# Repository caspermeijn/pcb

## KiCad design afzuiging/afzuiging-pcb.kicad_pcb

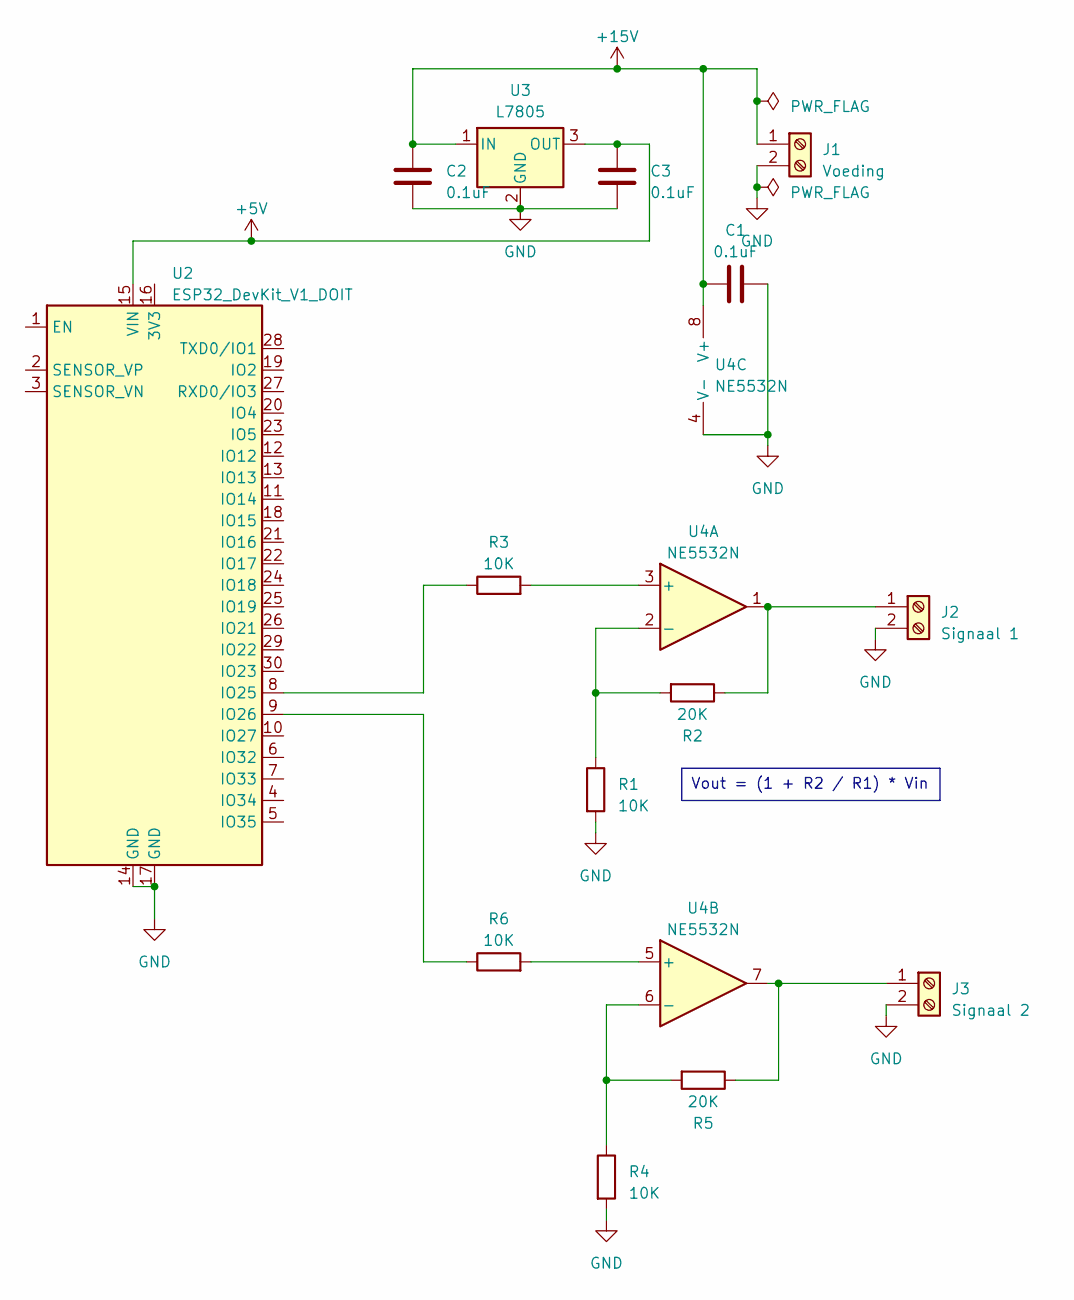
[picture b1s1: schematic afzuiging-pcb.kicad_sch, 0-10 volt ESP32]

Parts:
C1, C2, C3: 0.1uF; C_Disc_D4.7mm_W2.5mm_P5.00mm
J1: Voeding; TerminalBlock_RND_205-00001_1x02_P5.00mm_Horizontal
J2: Signaal 1; TerminalBlock_RND_205-00001_1x02_P5.00mm_Horizontal
J3: Signaal 2; TerminalBlock_RND_205-00001_1x02_P5.00mm_Horizontal
R1, R3, R4, R6: 10K; R_Axial_DIN0207_L6.3mm_D2.5mm_P10.16mm_Horizontal
R2, R5: 20K; R_Axial_DIN0207_L6.3mm_D2.5mm_P10.16mm_Horizontal
U2: ESP32_DevKit_V1_DOIT; esp32_devkit_v1_doit
U3: L7805; TO-220F-3_Horizontal_TabDown
U4: NE5532N; DIP-8_W7.62mm

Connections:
+5V: C3.1, U2.15 (VIN), U3.3 (OUT)
+15V: C1.1, C2.1, J1.1, U3.1 (IN), U4.8 (V+)
GND: C1.2, C2.2, C3.2, J1.2, J2.2, J3.2, R1.2, R4.2, U2.14 (GND), U2.17 (GND), U3.2 (GND), U4.4 (V-)
unnamed: J2.1, R2.1, U4.1
unnamed: J3.1, R5.1, U4.7
unnamed: R3.1, U2.8 (IO25)
unnamed: R6.1, U2.9 (IO26)
unnamed: R3.2, U4.3 (+)
unnamed: R1.1, R2.2, U4.2 (-)
unnamed: R6.2, U4.5 (+)
unnamed: R4.1, R5.2, U4.6 (-)

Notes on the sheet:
Vout = (1 + R2 / R1) * Vin

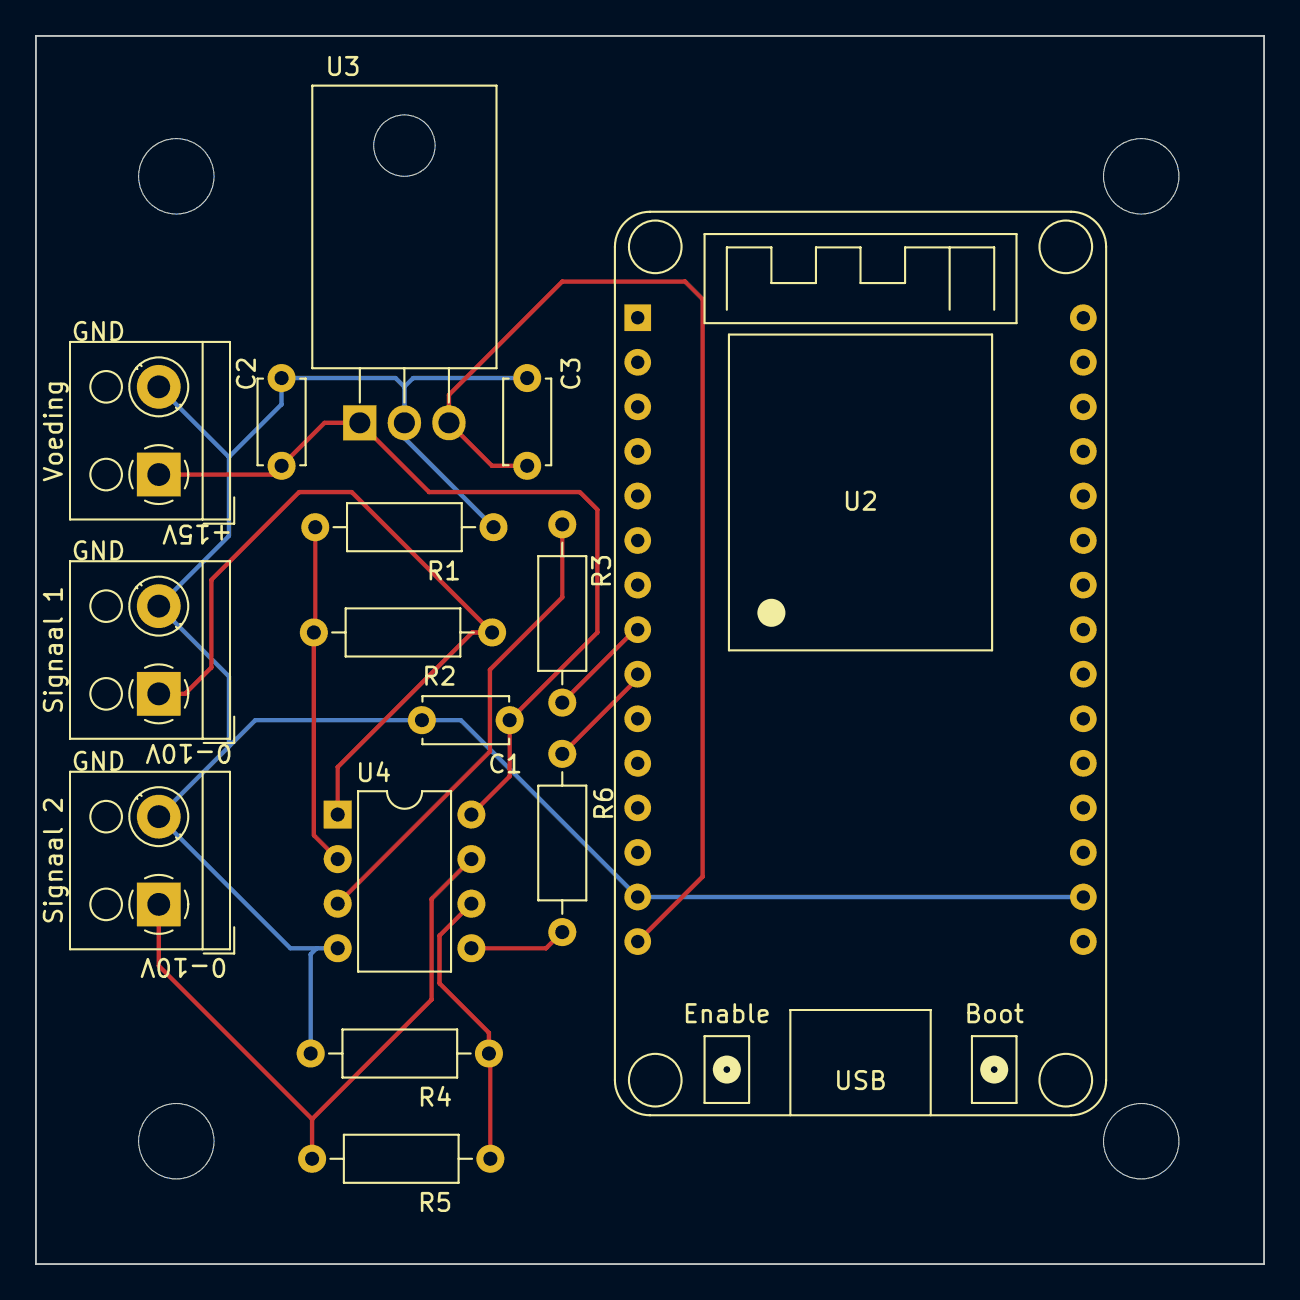
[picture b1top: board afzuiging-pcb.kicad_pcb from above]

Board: 2 copper layers, 70.0 x 70.0 mm, 15 parts (0 on the bottom side), 11 nets.

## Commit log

2023-02-24 Add afzuiging PCB
2023-04-02 Use OpAmp NE5532N
    NE5532N can actually be used for 10 volt. MCP6002 has a maximum voltage of 6 volt.
